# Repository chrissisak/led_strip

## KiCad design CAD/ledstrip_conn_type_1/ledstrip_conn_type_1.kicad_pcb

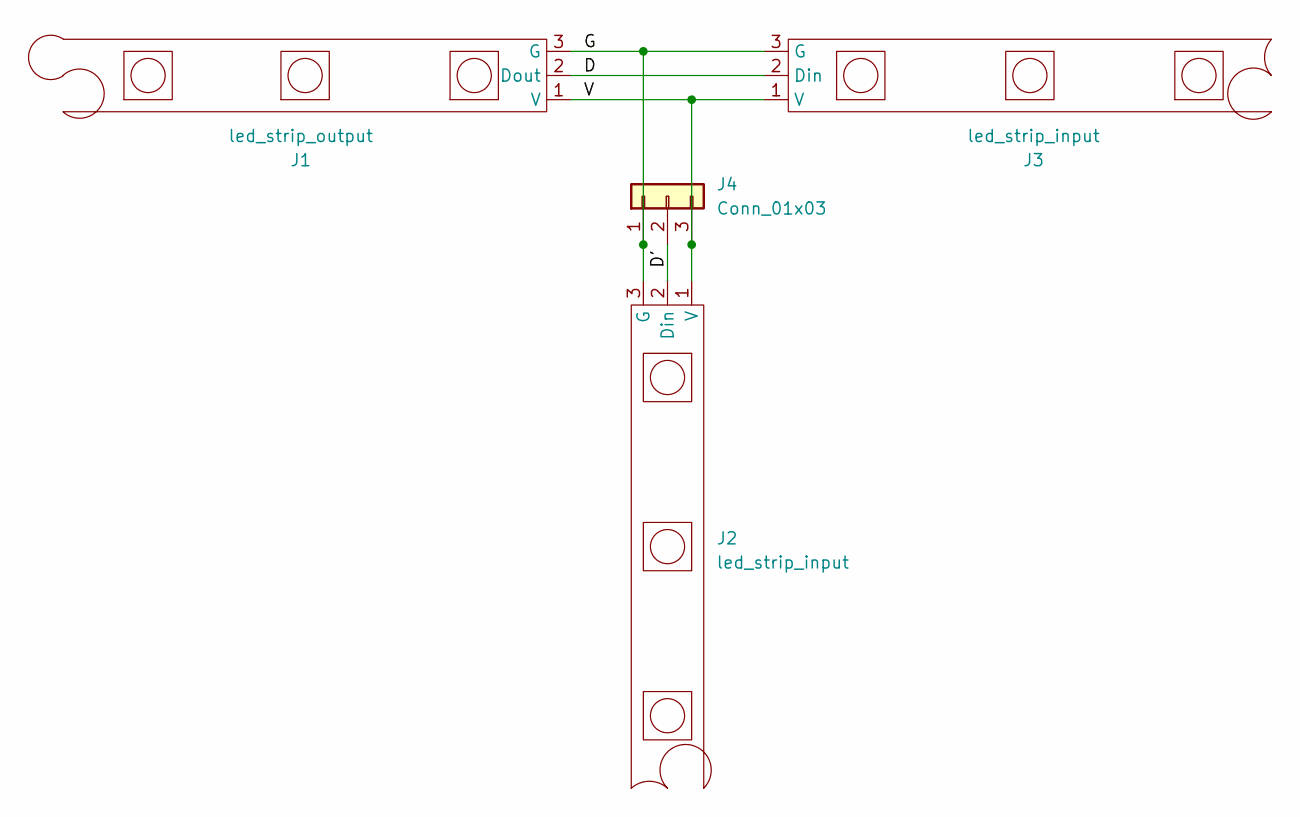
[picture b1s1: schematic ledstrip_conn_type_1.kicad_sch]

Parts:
J1: led_strip_output; strip_print_output
J2, J3: led_strip_input; strip_print_input
J4: Conn_01x03; PinHeader_1x03_P2.54mm_Vertical

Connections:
/D: J1.2 (Dout), J3.2 (Din)
/D': J2.2 (Din), J4.2
/G: J1.3 (G), J2.3 (G), J3.3 (G), J4.1
/V: J1.1 (V), J2.1 (V), J3.1 (V), J4.3

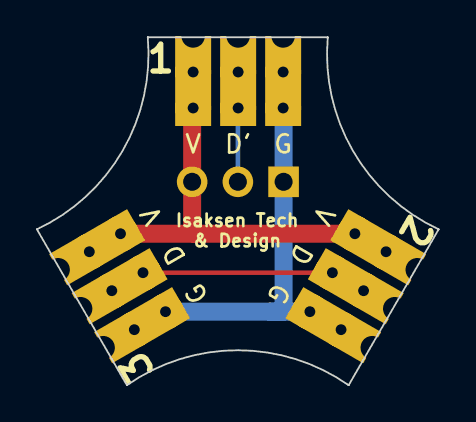
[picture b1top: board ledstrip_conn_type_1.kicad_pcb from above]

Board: 2 copper layers, 22.3 x 19.3 mm, 4 parts (1 on the bottom side), 4 nets.

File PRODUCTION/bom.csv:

Designator,Footprint,Quantity,Value,LCSC Part #
J1,strip_print_output,1,led_strip_output,
"J2, J3",strip_print_input,2,led_strip_input,
J4,PinHeader_1x03_P2.54mm_Vertical,1,Conn_01x03,

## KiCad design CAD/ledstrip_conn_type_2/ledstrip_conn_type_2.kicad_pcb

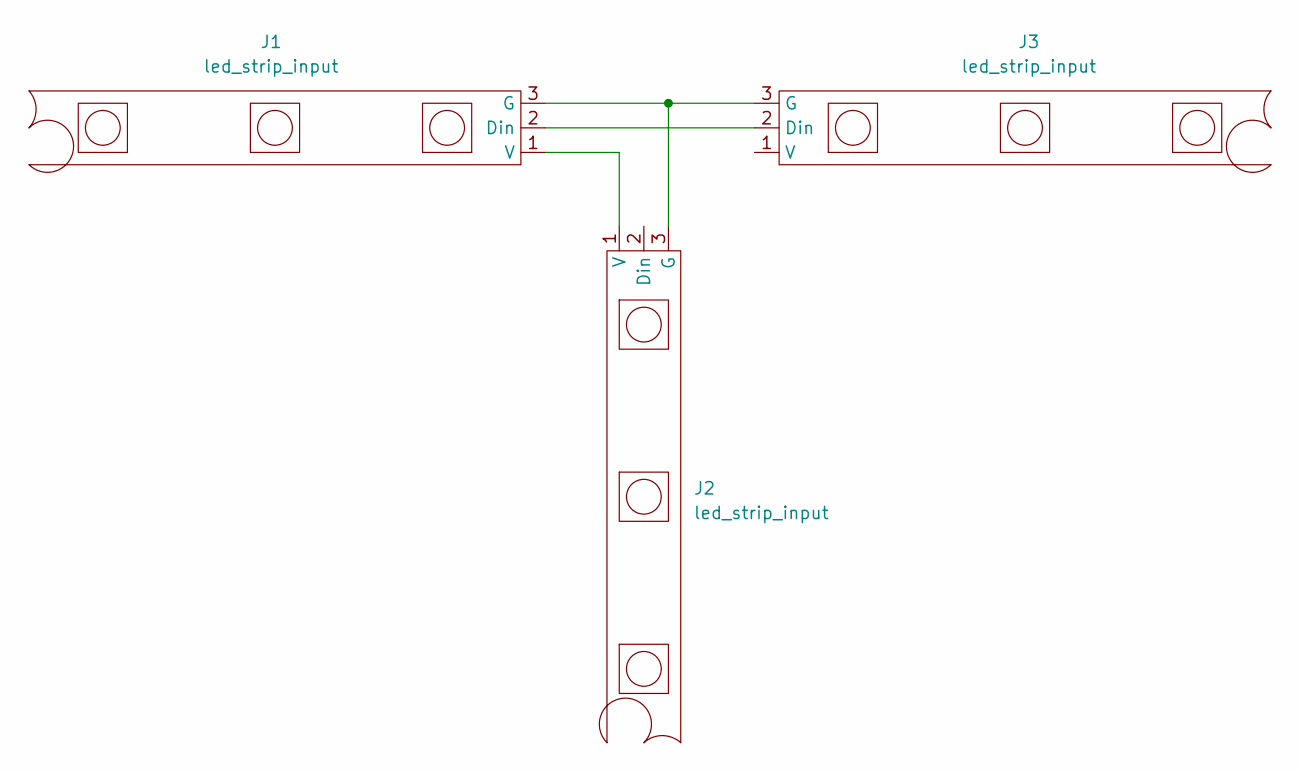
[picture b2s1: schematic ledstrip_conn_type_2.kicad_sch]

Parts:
J1, J2, J3: led_strip_input; strip_print_input

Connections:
unnamed: J1.1 (V), J2.1 (V)
unnamed: J1.2 (Din), J3.2 (Din)
unnamed: J1.3 (G), J2.3 (G), J3.3 (G)

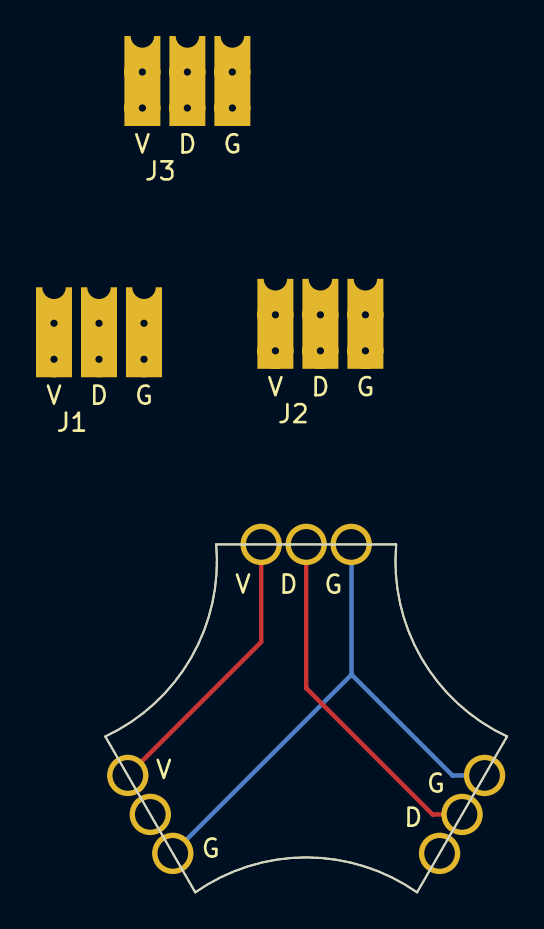
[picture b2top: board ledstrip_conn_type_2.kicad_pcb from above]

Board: 2 copper layers, 22.3 x 19.3 mm, 4 parts (0 on the bottom side), 3 nets.

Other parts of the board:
**: led_cube

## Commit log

2023-02-09 Feat: Transfered the project to new project struct
2023-02-09 Fix: Changed licence name
2023-02-09 Feat: Restructured project to two models
2023-02-09 Feat: Restructuring
2023-02-09 Feat: Library mess fixed
2023-02-09 feat: Added another led connector
2023-02-09 fix: direction of ledstrips
2023-02-10 Feat: New design, single connector
2023-02-12 feat: added wires to pcb
2023-02-13 Feat:Changed tracewidth, added pictures, prodfiles
2023-02-13 feat: added personal customization to pcb
